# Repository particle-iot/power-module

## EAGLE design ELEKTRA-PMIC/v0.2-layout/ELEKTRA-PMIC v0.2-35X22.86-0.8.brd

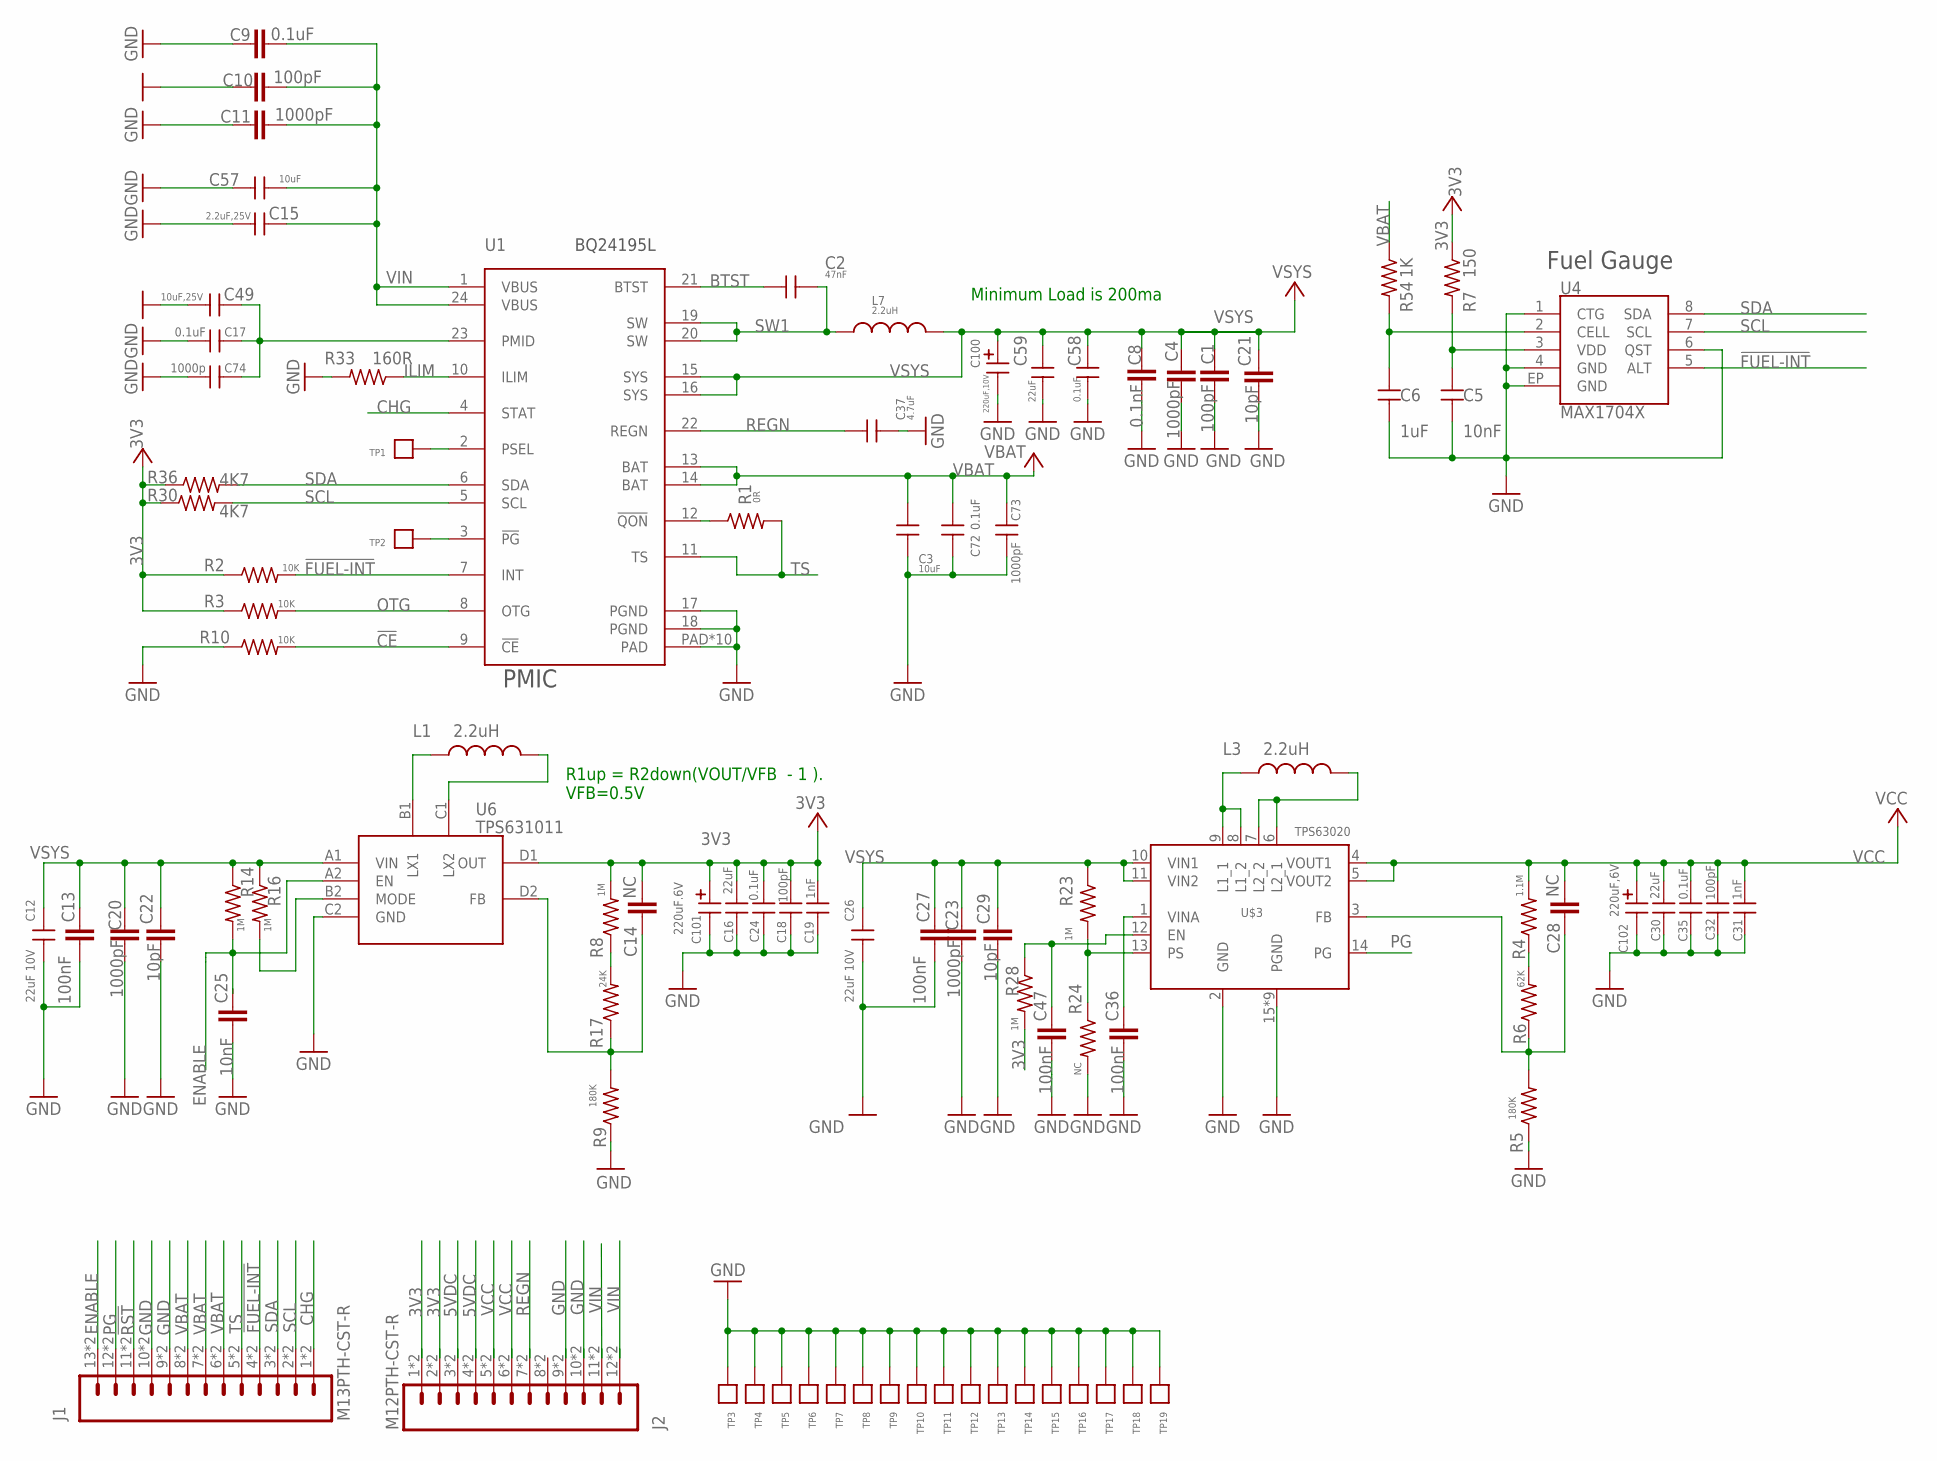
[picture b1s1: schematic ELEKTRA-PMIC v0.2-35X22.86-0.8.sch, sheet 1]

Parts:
C1, C10: 100pF; C0402_B
C2: 47nF; C-0402
C3: 10uF; C0805
C4, C11, C20, C23: 1000pF; C0402_B
C5: 10nF; C0402
C6: 1uF; C0402
C8: 0.1nF; C0402_B
C9: 0.1uF; C0402_B
C12, C26: 22uF 10V; C0805
C13, C27, C36, C47: 100nF; C0402_B
C14, C28: NC; C0402_B
C15: 2.2uF,25V; C-0603A
C16, C30: 22uF; C-0603A
C17, C24, C35, C58: 0.1uF; C0402
C18, C32: 100pF; C0402
C19, C31: 1nF; C0402
C21, C22, C29: 10pF; C0402_B
C25: 10nF; C0402_B
C37: 4.7uF; C0402
C49: 10uF,25V; C-0603A
C57: 10uF; C-0603A
C59: 22uF; C0603
C72: 0.1uF; C-0402
C73: 1000pF; C-0402
C74: 1000p; C-0402
C100: 220uF,10V; CASE-B
C101: 220uF.6V; CASE-B
C102: 220uF,6V; CASE-B
J1: M13PTH-CST-R; 1X13-CASTELLATED
J2: M12PTH-CST-R; 1X12-CASTELLATED
L1, L3: 2.2uH; INDUCTOR-VLS-E
L7: 2.2uH; INDUCTOR-4040
R1: 0R; R0402_B
R2, R3, R10: 10K; R0402_B
R4: 1.1M; R0402_B
R5, R9: 180K; R0402_B
R6: 62K; R0402_B
R7: 150; R0402_B
R8, R14, R16, R23, R28: 1M; R0402_B
R17: 24K; R0402_B
R24: NC; R0402_B
R30, R36: 4K7; R0402_B
R33: 160R; R0402_B
R54: 1K; R0402_B
TP1, TP2: TPTP; TP
TP3, TP4, TP5, TP6, TP7, TP8, TP9, TP10, TP11, TP12, TP13, TP14, TP15, TP16, TP17, TP18, TP19: TP0.4MM
U1: BQ24195L; QFN24
U4: MAX1704X; TDFN-8
U6: TPS631011; DSBGA
U$3: TPS63020

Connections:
3V3: C14.2, C16.1, C18.1, C19.1, C24.1, C101.P$1 (1), J2.1, J2.2, J2.@1 (1), J2.@2 (2), R2.1, R3.1, R7.1, R8.2, R28.2, R30.1, R36.1, U6.D1 (OUT)
5VDC: J2.3, J2.4, J2.@3 (3), J2.@4 (4)
!CE: R10.2, U1.9 (!CE)
!FUEL-INT: J1.4, J1.@4 (4), R2.2, U1.7 (INT), U4.5 (ALT)
!RST: J1.11, J1.@11 (11)
BTST: C2.1, U1.21 (BTST)
CHG: J1.1, J1.@1 (1), U1.4 (STAT)
ENABLE: C25.2, J1.13, J1.@13 (13), R14.2, U6.A2 (EN)
GND: C1.1, C3.2, C4.1, C5.2, C6.2, C8.1, C9.1, C10.1, C11.1, C12.2, C13.1, C15.2, C16.2, C17.1, C18.2, C19.2, C20.1, C21.1, C22.1, C23.1, C24.2, C25.1, C26.2, C27.1, C29.1, C30.2, C31.2, C32.2, C35.2, C36.1, C37.2, C47.1, C49.2, C57.2, C58.2, C59.2, C72.2, C73.2, C74.1, C100.P$2 (2), C101.P$2 (2), C102.P$2 (2), J1.9, J1.10, J1.@9 (9), J1.@10 (10), J2.9, J2.10, J2.@9 (9), J2.@10 (10), R5.1, R9.1, R10.1, R24.2, R33.2, TP3.P$1, TP4.P$1, TP5.P$1, TP6.P$1, TP7.P$1, TP8.P$1, TP9.P$1, TP10.P$1, TP11.P$1, TP12.P$1, TP13.P$1, TP14.P$1, TP15.P$1, TP16.P$1, TP17.P$1, TP18.P$1, TP19.P$1, U1.17 (PGND), U1.18 (PGND), U1.PAD, U1.PAD@1 (PAD), U1.PAD@2 (PAD), U1.PAD@3 (PAD), U1.PAD@4 (PAD), U1.PAD@5 (PAD), U1.PAD@6 (PAD), U1.PAD@7 (PAD), U1.PAD@8 (PAD), U1.PAD@9 (PAD), U4.1 (CTG), U4.4 (GND), U4.6 (QST), U4.EP (GND)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
ILIM: R33.1, U1.10 (ILIM)
unnamed: R1.1, U1.12 (!QON)
unnamed: C17.2, C49.1, C74.2, U1.23 (PMID)
unnamed: TP2.P$1, U1.3 (!PG)
unnamed: C14.1, R9.2, R17.1, U6.D2 (FB)
unnamed: C28.1, R5.2, R6.1, U$3.3 (FB)
unnamed: TP1.P$1, U1.2 (PSEL)
unnamed: R8.1, R17.2
unnamed: R4.1, R6.2
unnamed: L3.P$1 (1), U$3.8 (L1_2), U$3.9 (L1_1)
unnamed: L1.P$1 (1), U6.B1 (LX1)
unnamed: R16.2, U6.B2 (MODE)
unnamed: L3.P$2 (2), U$3.6 (L2_1), U$3.7 (L2_2)
unnamed: L1.P$2 (2), U6.C1 (LX2)
unnamed: C36.2, U$3.1 (VINA)
unnamed: C47.2, R28.1, U$3.12 (EN)
unnamed: R23.2, R24.1, U$3.13 (PS)
unnamed: C5.1, R7.2, U4.3 (VDD)
unnamed: C6.1, R54.2, U4.2 (CELL)
OTG: R3.2, U1.8 (OTG)
PG: J1.12, J1.@12 (12), U$3.14 (PG)
REGN: C37.1, J2.7, J2.@7 (7), U1.22 (REGN)
SCL: J1.2, J1.@2 (2), R30.2, U1.5 (SCL), U4.7 (SCL)
SDA: J1.3, J1.@3 (3), R36.2, U1.6 (SDA), U4.8 (SDA)
SW1: C2.2, L7.P$1 (1), U1.19 (SW), U1.20 (SW)
TS: J1.5, J1.@5 (5), R1.2, U1.11 (TS)
VBAT: C3.1, C72.1, C73.1, J1.6, J1.7, J1.8, J1.@6 (6), J1.@7 (7), J1.@8 (8), R54.1, U1.13 (BAT), U1.14 (BAT)
VCC: C28.2, C30.1, C31.1, C32.1, C35.1, C102.P$1 (1), J2.5, J2.6, J2.@5 (5), J2.@6 (6), R4.2, U$3.4 (VOUT1), U$3.5 (VOUT2)
VIN: C9.2, C10.2, C11.2, C15.1, C57.1, J2.11, J2.12, J2.@11 (11), J2.@12 (12), U1.1 (VBUS), U1.24 (VBUS)
VSYS: C1.2, C4.2, C8.2, C12.1, C13.2, C20.2, C21.2, C22.2, C23.2, C26.1, C27.2, C29.2, C58.1, C59.1, C100.P$1 (1), L7.P$2 (2), R14.1, R16.1, R23.1, U1.15 (SYS), U1.16 (SYS), U6.A1 (VIN), U$3.10 (VIN1), U$3.11 (VIN2)

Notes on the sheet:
Minimum Load is 200ma
PMIC
Fuel Gauge
R1up = R2down(VOUT/VFB - 1 ). VFB=0.5V

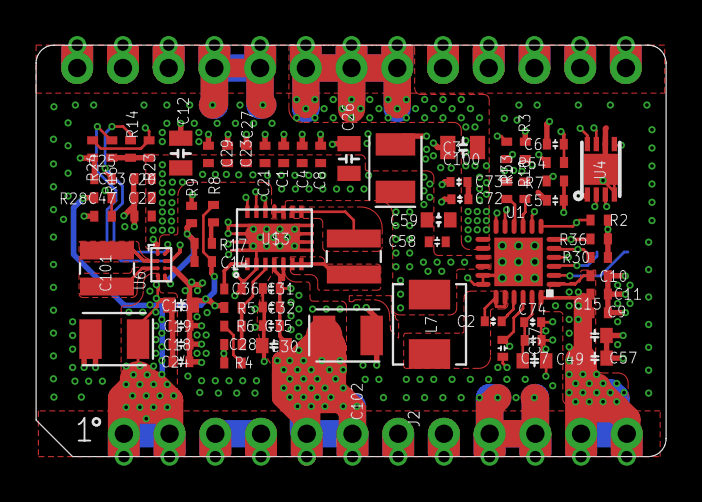
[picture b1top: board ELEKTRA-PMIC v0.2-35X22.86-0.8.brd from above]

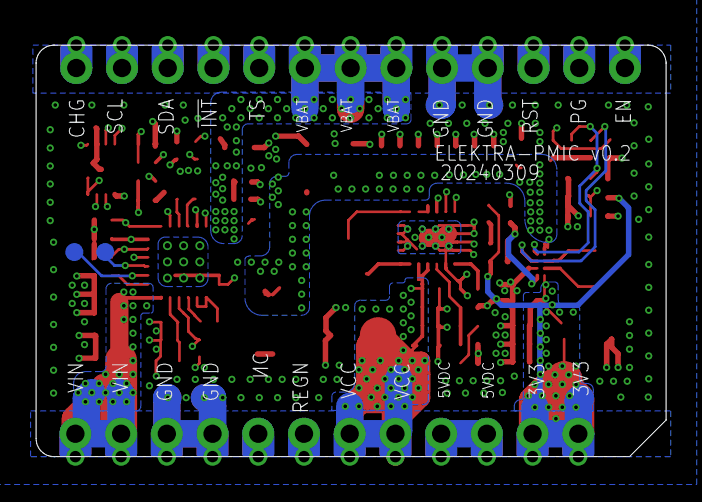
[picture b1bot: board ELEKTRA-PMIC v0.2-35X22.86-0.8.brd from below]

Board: 4 copper layers, 35.0 x 22.9 mm, 93 parts (19 on the bottom side), 39 nets.

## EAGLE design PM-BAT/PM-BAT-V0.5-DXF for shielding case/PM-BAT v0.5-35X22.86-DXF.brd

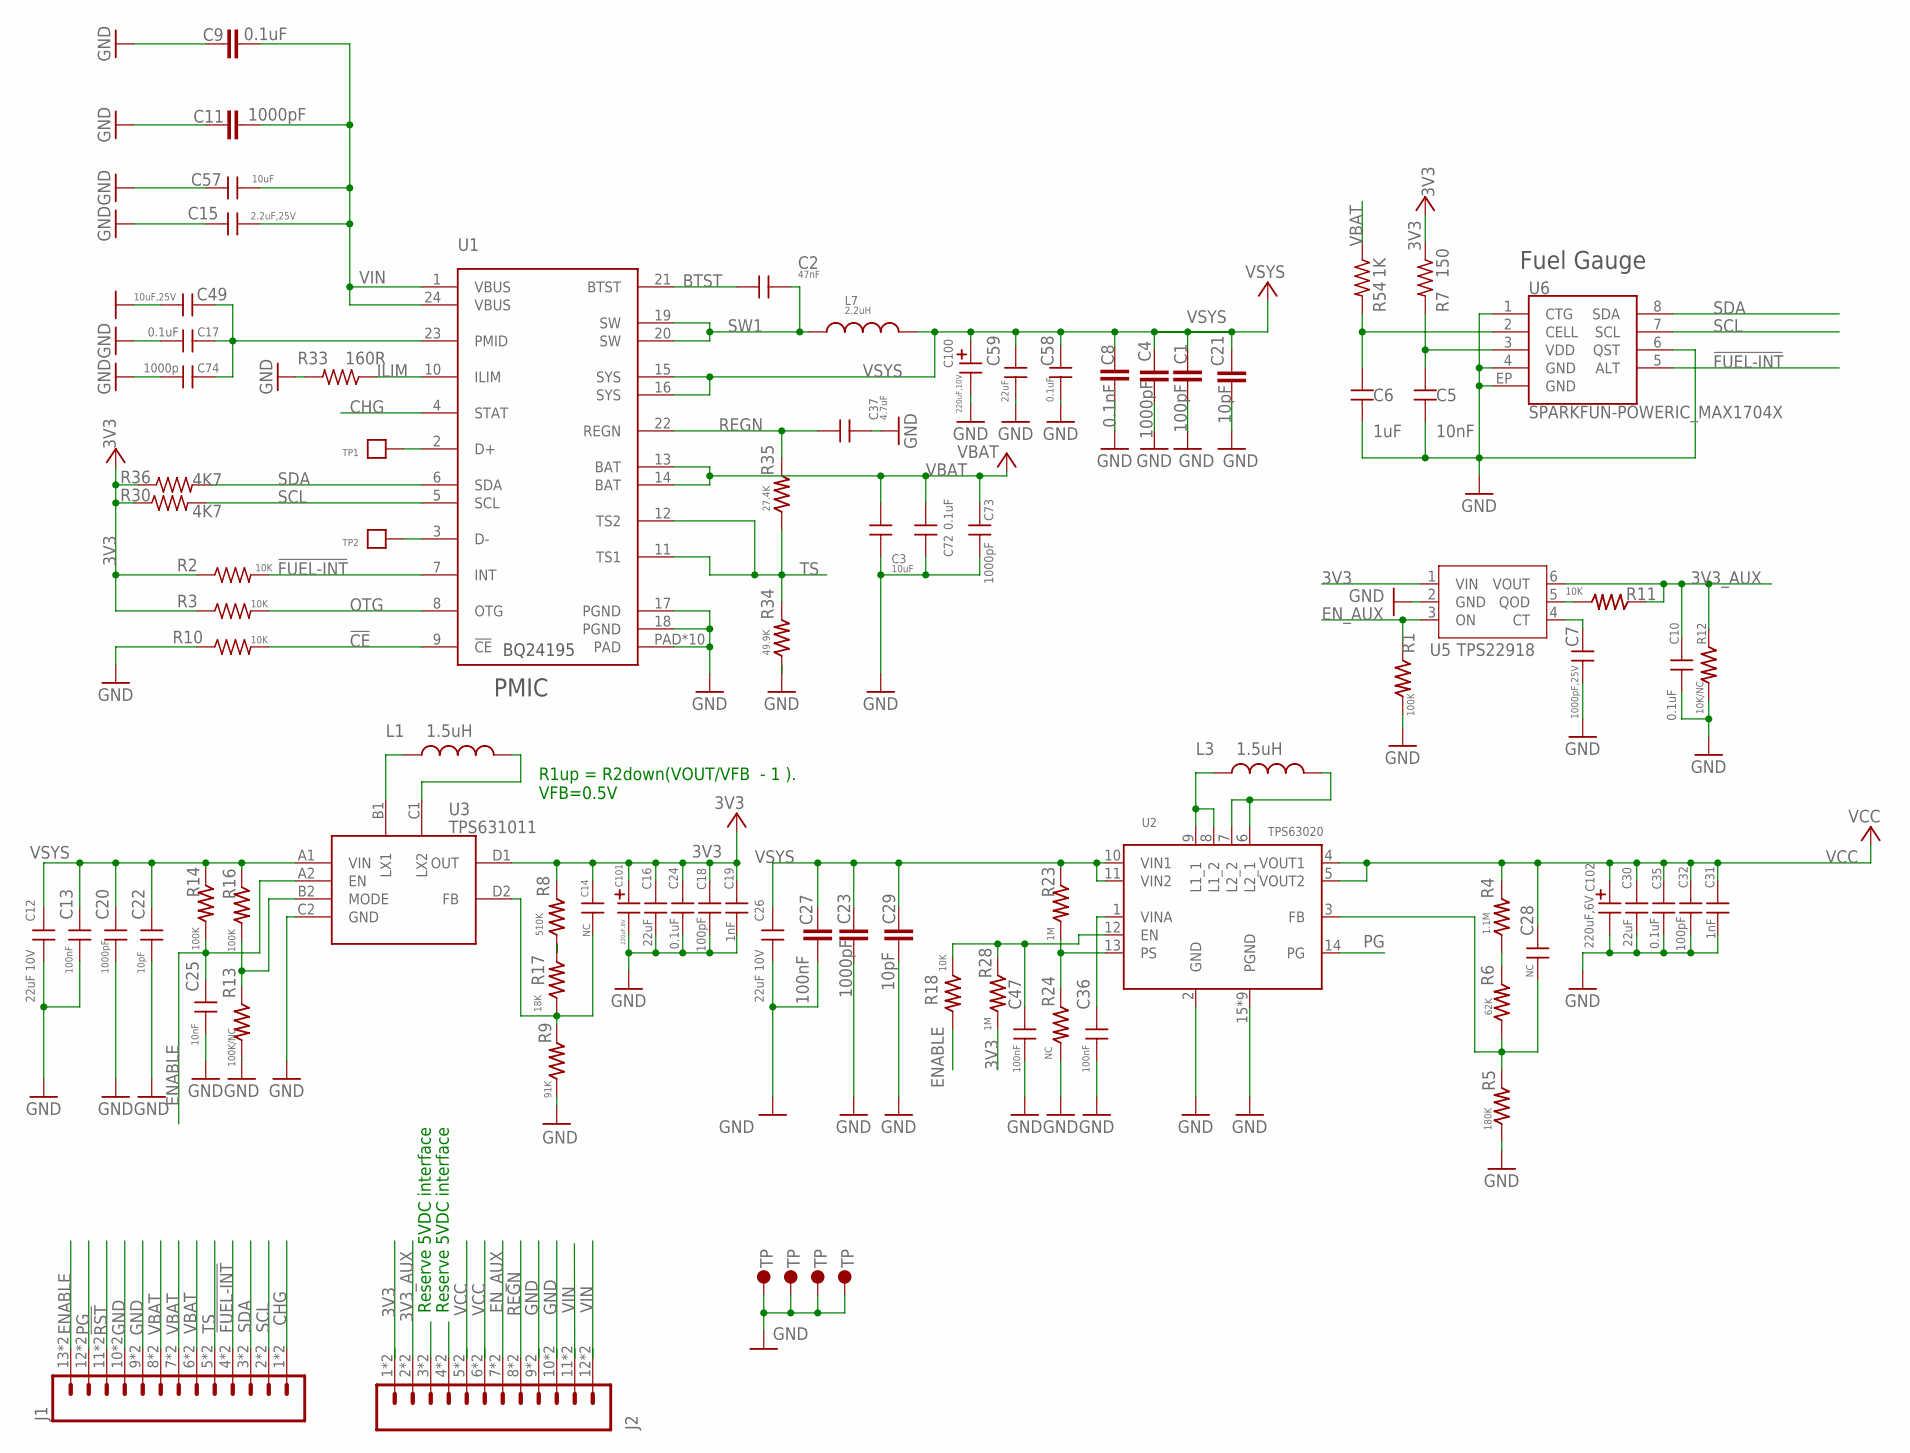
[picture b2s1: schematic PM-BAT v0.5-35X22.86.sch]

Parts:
C1: 100pF; C0402_B
C2: 47nF; C-0402
C3: 10uF; C0805
C4, C11, C23: 1000pF; C0402_B
C5: 10nF; C0402
C6: 1uF; C0402
C7: 1000pF,25V; C0402
C8: 0.1nF; C0402_B
C9: 0.1uF; C0402_B
C10: 0.1uF; C0201-N
C12, C26: 22uF 10V; C0603
C13, C36, C47: 100nF; C0201-N
C14, C28: NC; C0201-N
C15: 2.2uF,25V; C-0603A
C16, C30: 22uF; C-0603A
C17, C24, C35, C58: 0.1uF; C0402
C18, C32: 100pF; C0402
C19, C31: 1nF; C0402
C20: 1000pF; C0201-N
C21, C29: 10pF; C0402_B
C22: 10pF; C0201-N
C25: 10nF; C0201-N
C27: 100nF; C0402_B
C37: 4.7uF; C0402
C49: 10uF,25V; C-0603A
C57: 10uF; C-0603A
C59: 22uF; C0603
C72: 0.1uF; C-0402
C73: 1000pF; C-0402
C74: 1000p; C-0402
C100: 220uF,10V; CASE-B
C101: 220uF.6V; CASE-B
C102: 220uF,6V; CASE-B
J1: M13PTH-CST-R; 1X13-CASTELLATED
J2: M12PTH-CST-R; 1X12-CASTELLATED
L1, L3: 1.5uH; INDUCTOR-2520
L7: 2.2uH; INDUCTOR-4040
R1, R14, R16: 100K; R0201-N
R2, R3, R10: 10K; R0402_B
R4: 1.1M; R0201-N
R5: 180K; R0201-N
R6: 62K; R0201-N
R7: 150; R0402_B
R8: 510K; R0201-N
R9: 91K; R0201-N
R11, R18: 10K; R0201-N
R12: 10K/NC; R0201-N
R13: 100K/NC; R0201-N
R17: 18K; R0201-N
R23, R28: 1M; R0201-N
R24: NC; R0201-N
R30, R36: 4K7; R0402_B
R33: 160R; R0402_B
R34: 49.9K; R0201-N
R35: 27.4K; R0201-N
R54: 1K; R0402_B
TP1, TP2: TP1311MM; TP-1311MM
U1: BQ24195; ELECTRON_QFN24
U2: TPS63020
U3: TPS631011; DSBGA
U5: TPS22918; SOT-23-6
U6: SPARKFUN-POWERIC_MAX1704X; SPARKFUN-POWERIC_TDFN-8
U$1, U$2, U$4, U$5: TP; TP_2.33X1.37

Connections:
3V3: C14.1, C16.1, C18.1, C19.1, C24.1, C101.P$1 (1), J2.1, J2.@1 (1), R2.1, R3.1, R7.1, R8.2, R28.2, R30.1, R36.1, U3.D1 (OUT), U5.1 (VIN)
3V3_AUX: C10.1, J2.2, J2.@2 (2), R11.1, R12.1, U5.6 (VOUT)
!CE: R10.2, U1.9 (!CE)
!FUEL-INT: J1.4, J1.@4 (4), R2.2, U1.7 (INT), U6.5 (ALT)
!RST: J1.11, J1.@11 (11)
BTST: C2.1, U1.21 (BTST)
CHG: J1.1, J1.@1 (1), U1.4 (STAT)
ENABLE: C25.1, J1.13, J1.@13 (13), R14.2, R18.2, U3.A2 (EN)
EN_AUX: J2.7, J2.@7 (7), R1.1, U5.3 (ON)
GND: C1.1, C3.2, C4.1, C5.2, C6.2, C7.2, C8.1, C9.1, C10.2, C11.1, C12.2, C13.2, C15.2, C16.2, C17.1, C18.2, C19.2, C20.2, C21.1, C22.2, C23.1, C24.2, C25.2, C26.2, C27.1, C29.1, C30.2, C31.2, C32.2, C35.2, C36.2, C37.2, C47.2, C49.2, C57.2, C58.2, C59.2, C72.2, C73.2, C74.1, C100.P$2 (2), C101.P$2 (2), C102.P$2 (2), J1.9, J1.10, J1.@9 (9), J1.@10 (10), J2.9, J2.10, J2.@9 (9), J2.@10 (10), R1.2, R5.1, R9.1, R10.1, R12.2, R13.2, R24.2, R33.2, R34.1, U1.17 (PGND), U1.18 (PGND), U1.PAD, U1.PAD@1 (PAD), U1.PAD@2 (PAD), U1.PAD@3 (PAD), U1.PAD@4 (PAD), U1.PAD@5 (PAD), U1.PAD@6 (PAD), U1.PAD@7 (PAD), U1.PAD@8 (PAD), U1.PAD@9 (PAD), U2.2 (GND), U2.15 (PGND), U2.16 (PGND), U2.17 (PGND), U2.18 (PGND), U2.19 (PGND), U2.20 (PGND), U2.21 (PGND), U2.22 (PGND), U2.23 (PGND), U3.C2 (GND), U5.2 (GND), U6.1 (CTG), U6.4 (GND), U6.6 (QST), U6.EP (GND)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
ILIM: R33.1, U1.10 (ILIM)
unnamed: J2.3, J2.@3 (3)
unnamed: C17.2, C49.1, C74.2, U1.23 (PMID)
unnamed: TP2.P$1, U1.3 (D-)
unnamed: C14.2, R9.2, R17.1, U3.D2 (FB)
unnamed: C28.2, R5.2, R6.1, U2.3 (FB)
unnamed: TP1.P$1, U1.2 (D+)
unnamed: R8.1, R17.2
unnamed: R4.1, R6.2
unnamed: J2.4, J2.@4 (4)
unnamed: L3.1, U2.8 (L1_2), U2.9 (L1_1)
unnamed: L1.1, U3.B1 (LX1)
unnamed: R13.1, R16.2, U3.B2 (MODE)
unnamed: L3.2, U2.6 (L2_1), U2.7 (L2_2)
unnamed: L1.2, U3.C1 (LX2)
unnamed: C7.1, U5.4 (CT)
unnamed: C36.1, U2.1 (VINA)
unnamed: R11.2, U5.5 (QOD)
unnamed: C47.1, R18.1, R28.1, U2.12 (EN)
unnamed: R23.2, R24.1, U2.13 (PS)
unnamed: C5.1, R7.2, U6.3 (VDD)
unnamed: C6.1, R54.2, U6.2 (CELL)
OTG: R3.2, U1.8 (OTG)
PG: J1.12, J1.@12 (12), U2.14 (PG)
REGN: C37.1, J2.8, J2.@8 (8), R35.2, U1.22 (REGN)
SCL: J1.2, J1.@2 (2), R30.2, U1.5 (SCL), U6.7 (SCL)
SDA: J1.3, J1.@3 (3), R36.2, U1.6 (SDA), U6.8 (SDA)
SW1: C2.2, L7.P$1 (1), U1.19 (SW), U1.20 (SW)
TS: J1.5, J1.@5 (5), R34.2, R35.1, U1.11 (TS1), U1.12 (TS2)
VBAT: C3.1, C72.1, C73.1, J1.6, J1.7, J1.8, J1.@6 (6), J1.@7 (7), J1.@8 (8), R54.1, U1.13 (BAT), U1.14 (BAT)
VCC: C28.1, C30.1, C31.1, C32.1, C35.1, C102.P$1 (1), J2.5, J2.6, J2.@5 (5), J2.@6 (6), R4.2, U2.4 (VOUT1), U2.5 (VOUT2)
VIN: C9.2, C11.2, C15.1, C57.1, J2.11, J2.12, J2.@11 (11), J2.@12 (12), U1.1 (VBUS), U1.24 (VBUS)
VSYS: C1.2, C4.2, C8.2, C12.1, C13.1, C20.1, C21.2, C22.1, C23.2, C26.1, C27.2, C29.2, C58.1, C59.1, C100.P$1 (1), L7.P$2 (2), R14.1, R16.1, R23.1, U1.15 (SYS), U1.16 (SYS), U2.10 (VIN1), U2.11 (VIN2), U3.A1 (VIN)

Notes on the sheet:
PMIC
Fuel Gauge
R1up = R2down(VOUT/VFB - 1 ). VFB=0.5V
Reserve 5VDC interface

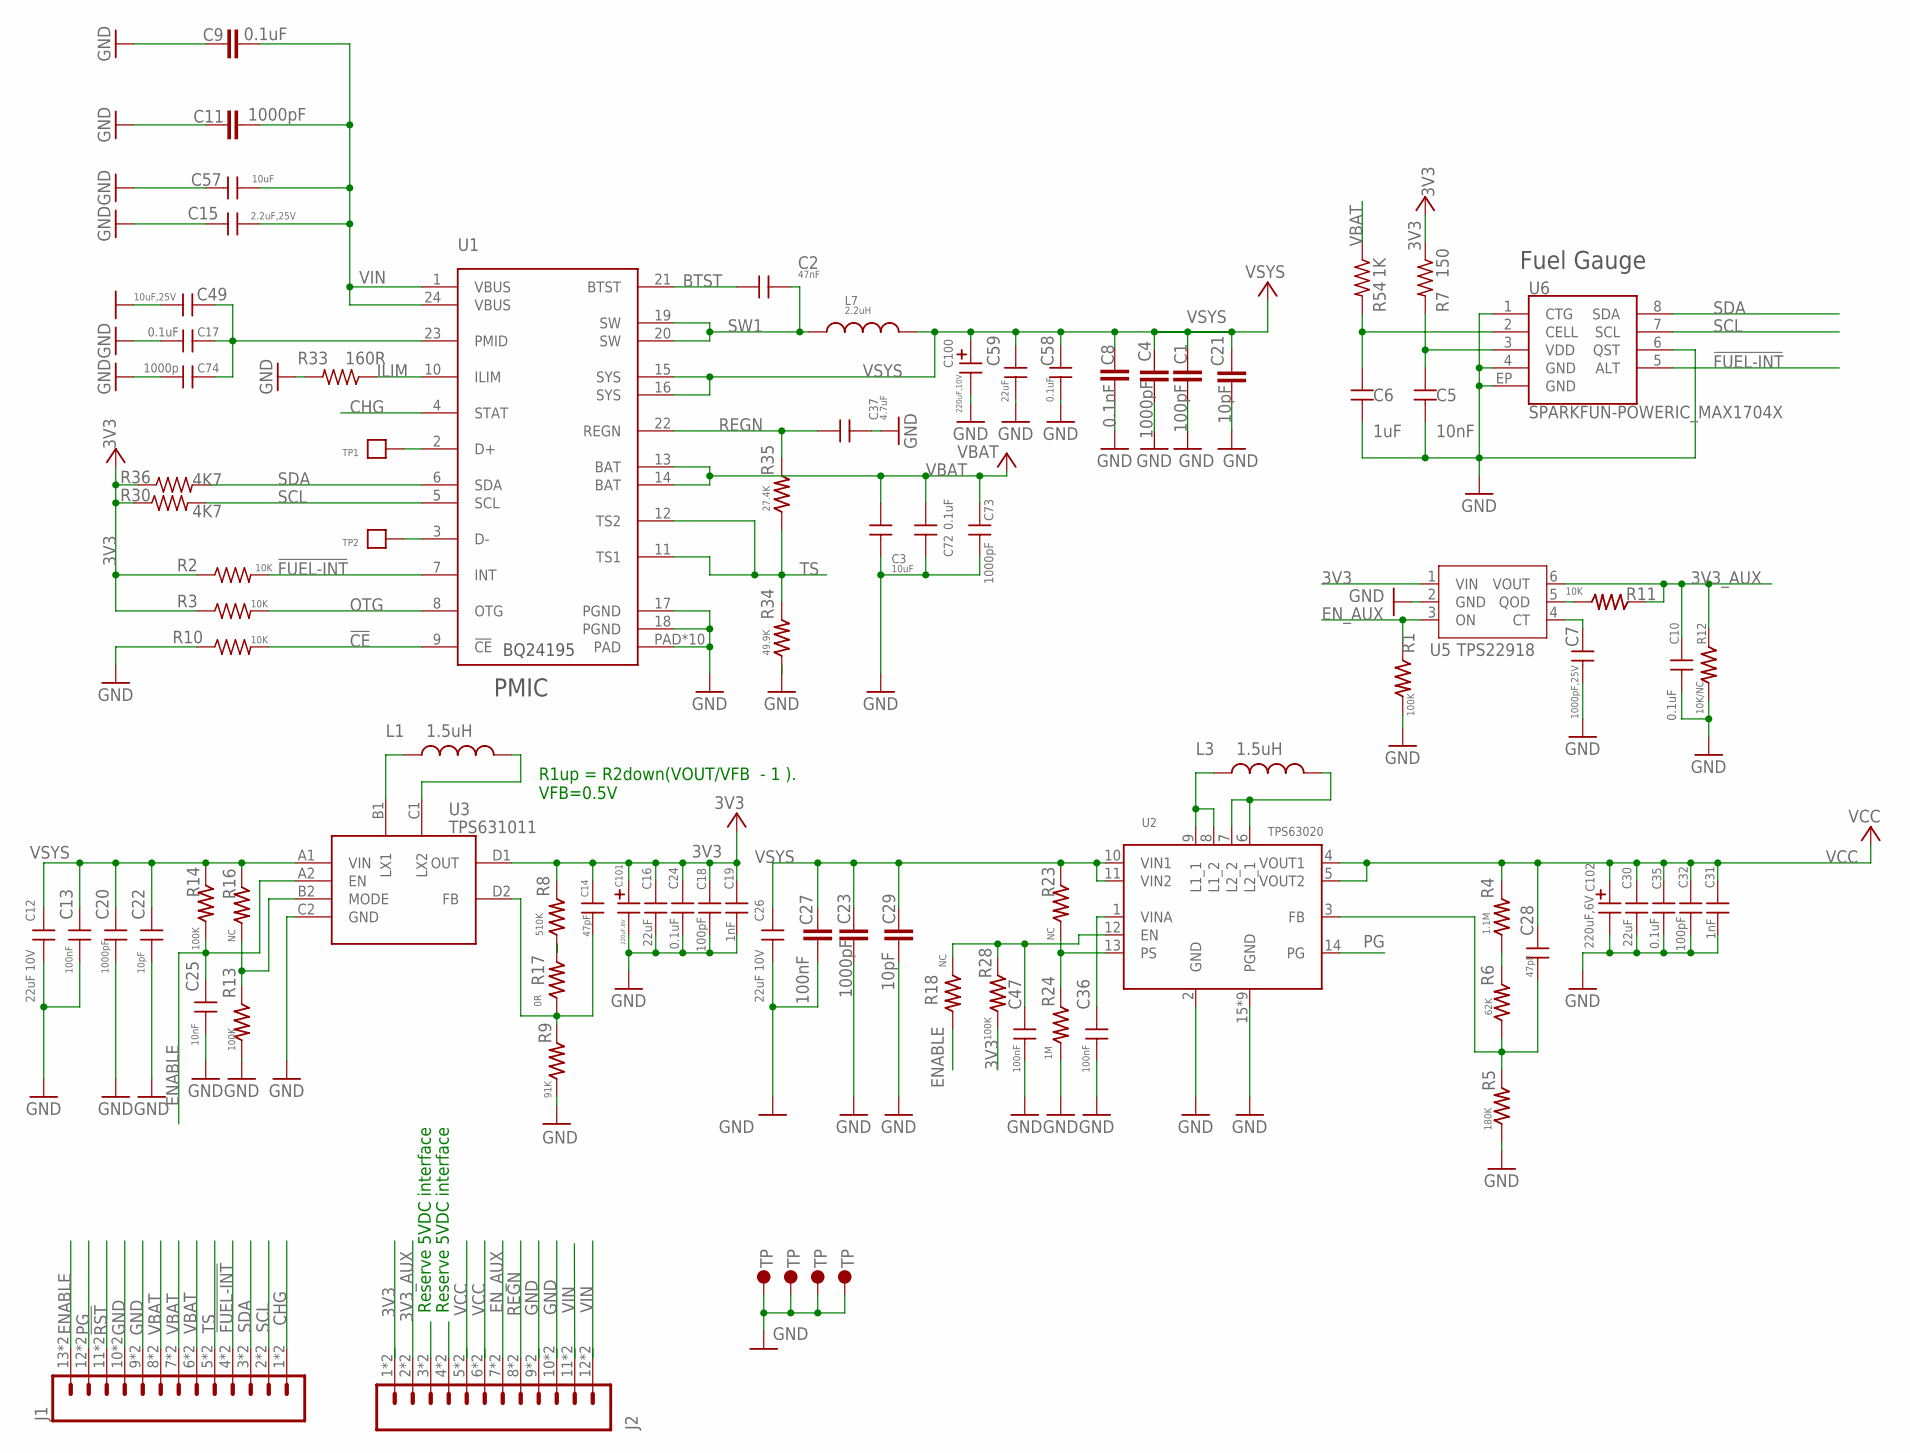
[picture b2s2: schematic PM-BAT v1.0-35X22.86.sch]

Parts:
C1: 100pF; C0402_B
C2: 47nF; C-0402
C3: 10uF; C0805
C4, C11, C23: 1000pF; C0402_B
C5: 10nF; C0402
C6: 1uF; C0402
C7: 1000pF,25V; C0402
C8: 0.1nF; C0402_B
C9: 0.1uF; C0402_B
C10: 0.1uF; C0201-N
C12, C26: 22uF 10V; C0603
C13, C36, C47: 100nF; C0201-N
C14, C28: 47pF; C0201-N
C15: 2.2uF,25V; C-0603A
C16, C30: 22uF; C-0603A
C17, C24, C35, C58: 0.1uF; C0402
C18, C32: 100pF; C0402
C19, C31: 1nF; C0402
C20: 1000pF; C0201-N
C21, C29: 10pF; C0402_B
C22: 10pF; C0201-N
C25: 10nF; C0201-N
C27: 100nF; C0402_B
C37: 4.7uF; C0402
C49: 10uF,25V; C-0603A
C57: 10uF; C-0603A
C59: 22uF; C0603
C72: 0.1uF; C-0402
C73: 1000pF; C-0402
C74: 1000p; C-0402
C100: 220uF,10V; CASE-B
C101: 220uF.6V; CASE-B
C102: 220uF,6V; CASE-B
J1: M13PTH-CST-R; 1X13-CASTELLATED
J2: M12PTH-CST-R; 1X12-CASTELLATED
L1, L3: 1.5uH; INDUCTOR-2520
L7: 2.2uH; INDUCTOR-4040
R1, R13, R14, R28: 100K; R0201-N
R2, R3, R10: 10K; R0402_B
R4: 1.1M; R0201-N
R5: 180K; R0201-N
R6: 62K; R0201-N
R7: 150; R0402_B
R8: 510K; R0201-N
R9: 91K; R0201-N
R11: 10K; R0201-N
R12: 10K/NC; R0201-N
R16, R18, R23: NC; R0201-N
R17: 0R; R0201-N
R24: 1M; R0201-N
R30, R36: 4K7; R0402_B
R33: 160R; R0402_B
R34: 49.9K; R0201-N
R35: 27.4K; R0201-N
R54: 1K; R0402_B
TP1, TP2: TP1311MM; TP-1311MM
U1: BQ24195; ELECTRON_QFN24
U2: TPS63020
U3: TPS631011; DSBGA
U5: TPS22918; SOT-23-6
U6: SPARKFUN-POWERIC_MAX1704X; SPARKFUN-POWERIC_TDFN-8
U$1, U$2, U$4, U$5: TP; TP_2.33X1.37

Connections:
3V3: C14.1, C16.1, C18.1, C19.1, C24.1, C101.P$1 (1), J2.1, J2.@1 (1), R2.1, R3.1, R7.1, R8.2, R28.2, R30.1, R36.1, U3.D1 (OUT), U5.1 (VIN)
3V3_AUX: C10.1, J2.2, J2.@2 (2), R11.1, R12.1, U5.6 (VOUT)
!CE: R10.2, U1.9 (!CE)
!FUEL-INT: J1.4, J1.@4 (4), R2.2, U1.7 (INT), U6.5 (ALT)
!RST: J1.11, J1.@11 (11)
BTST: C2.1, U1.21 (BTST)
CHG: J1.1, J1.@1 (1), U1.4 (STAT)
ENABLE: C25.1, J1.13, J1.@13 (13), R14.2, R18.2, U3.A2 (EN)
EN_AUX: J2.7, J2.@7 (7), R1.1, U5.3 (ON)
GND: C1.1, C3.2, C4.1, C5.2, C6.2, C7.2, C8.1, C9.1, C10.2, C11.1, C12.2, C13.2, C15.2, C16.2, C17.1, C18.2, C19.2, C20.2, C21.1, C22.2, C23.1, C24.2, C25.2, C26.2, C27.1, C29.1, C30.2, C31.2, C32.2, C35.2, C36.2, C37.2, C47.2, C49.2, C57.2, C58.2, C59.2, C72.2, C73.2, C74.1, C100.P$2 (2), C101.P$2 (2), C102.P$2 (2), J1.9, J1.10, J1.@9 (9), J1.@10 (10), J2.9, J2.10, J2.@9 (9), J2.@10 (10), R1.2, R5.1, R9.1, R10.1, R12.2, R13.2, R24.2, R33.2, R34.1, U1.17 (PGND), U1.18 (PGND), U1.PAD, U1.PAD@1 (PAD), U1.PAD@2 (PAD), U1.PAD@3 (PAD), U1.PAD@4 (PAD), U1.PAD@5 (PAD), U1.PAD@6 (PAD), U1.PAD@7 (PAD), U1.PAD@8 (PAD), U1.PAD@9 (PAD), U2.2 (GND), U2.15 (PGND), U2.16 (PGND), U2.17 (PGND), U2.18 (PGND), U2.19 (PGND), U2.20 (PGND), U2.21 (PGND), U2.22 (PGND), U2.23 (PGND), U3.C2 (GND), U5.2 (GND), U6.1 (CTG), U6.4 (GND), U6.6 (QST), U6.EP (GND)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
ILIM: R33.1, U1.10 (ILIM)
unnamed: J2.3, J2.@3 (3)
unnamed: C17.2, C49.1, C74.2, U1.23 (PMID)
unnamed: TP2.P$1, U1.3 (D-)
unnamed: C14.2, R9.2, R17.1, U3.D2 (FB)
unnamed: C28.2, R5.2, R6.1, U2.3 (FB)
unnamed: TP1.P$1, U1.2 (D+)
unnamed: R8.1, R17.2
unnamed: R4.1, R6.2
unnamed: J2.4, J2.@4 (4)
unnamed: L3.1, U2.8 (L1_2), U2.9 (L1_1)
unnamed: L1.1, U3.B1 (LX1)
unnamed: R13.1, R16.2, U3.B2 (MODE)
unnamed: L3.2, U2.6 (L2_1), U2.7 (L2_2)
unnamed: L1.2, U3.C1 (LX2)
unnamed: C7.1, U5.4 (CT)
unnamed: C36.1, U2.1 (VINA)
unnamed: R11.2, U5.5 (QOD)
unnamed: C47.1, R18.1, R28.1, U2.12 (EN)
unnamed: R23.2, R24.1, U2.13 (PS)
unnamed: C5.1, R7.2, U6.3 (VDD)
unnamed: C6.1, R54.2, U6.2 (CELL)
OTG: R3.2, U1.8 (OTG)
PG: J1.12, J1.@12 (12), U2.14 (PG)
REGN: C37.1, J2.8, J2.@8 (8), R35.2, U1.22 (REGN)
SCL: J1.2, J1.@2 (2), R30.2, U1.5 (SCL), U6.7 (SCL)
SDA: J1.3, J1.@3 (3), R36.2, U1.6 (SDA), U6.8 (SDA)
SW1: C2.2, L7.P$1 (1), U1.19 (SW), U1.20 (SW)
TS: J1.5, J1.@5 (5), R34.2, R35.1, U1.11 (TS1), U1.12 (TS2)
VBAT: C3.1, C72.1, C73.1, J1.6, J1.7, J1.8, J1.@6 (6), J1.@7 (7), J1.@8 (8), R54.1, U1.13 (BAT), U1.14 (BAT)
VCC: C28.1, C30.1, C31.1, C32.1, C35.1, C102.P$1 (1), J2.5, J2.6, J2.@5 (5), J2.@6 (6), R4.2, U2.4 (VOUT1), U2.5 (VOUT2)
VIN: C9.2, C11.2, C15.1, C57.1, J2.11, J2.12, J2.@11 (11), J2.@12 (12), U1.1 (VBUS), U1.24 (VBUS)
VSYS: C1.2, C4.2, C8.2, C12.1, C13.1, C20.1, C21.2, C22.1, C23.2, C26.1, C27.2, C29.2, C58.1, C59.1, C100.P$1 (1), L7.P$2 (2), R14.1, R16.1, R23.1, U1.15 (SYS), U1.16 (SYS), U2.10 (VIN1), U2.11 (VIN2), U3.A1 (VIN)

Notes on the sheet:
PMIC
Fuel Gauge
R1up = R2down(VOUT/VFB - 1 ). VFB=0.5V
Reserve 5VDC interface

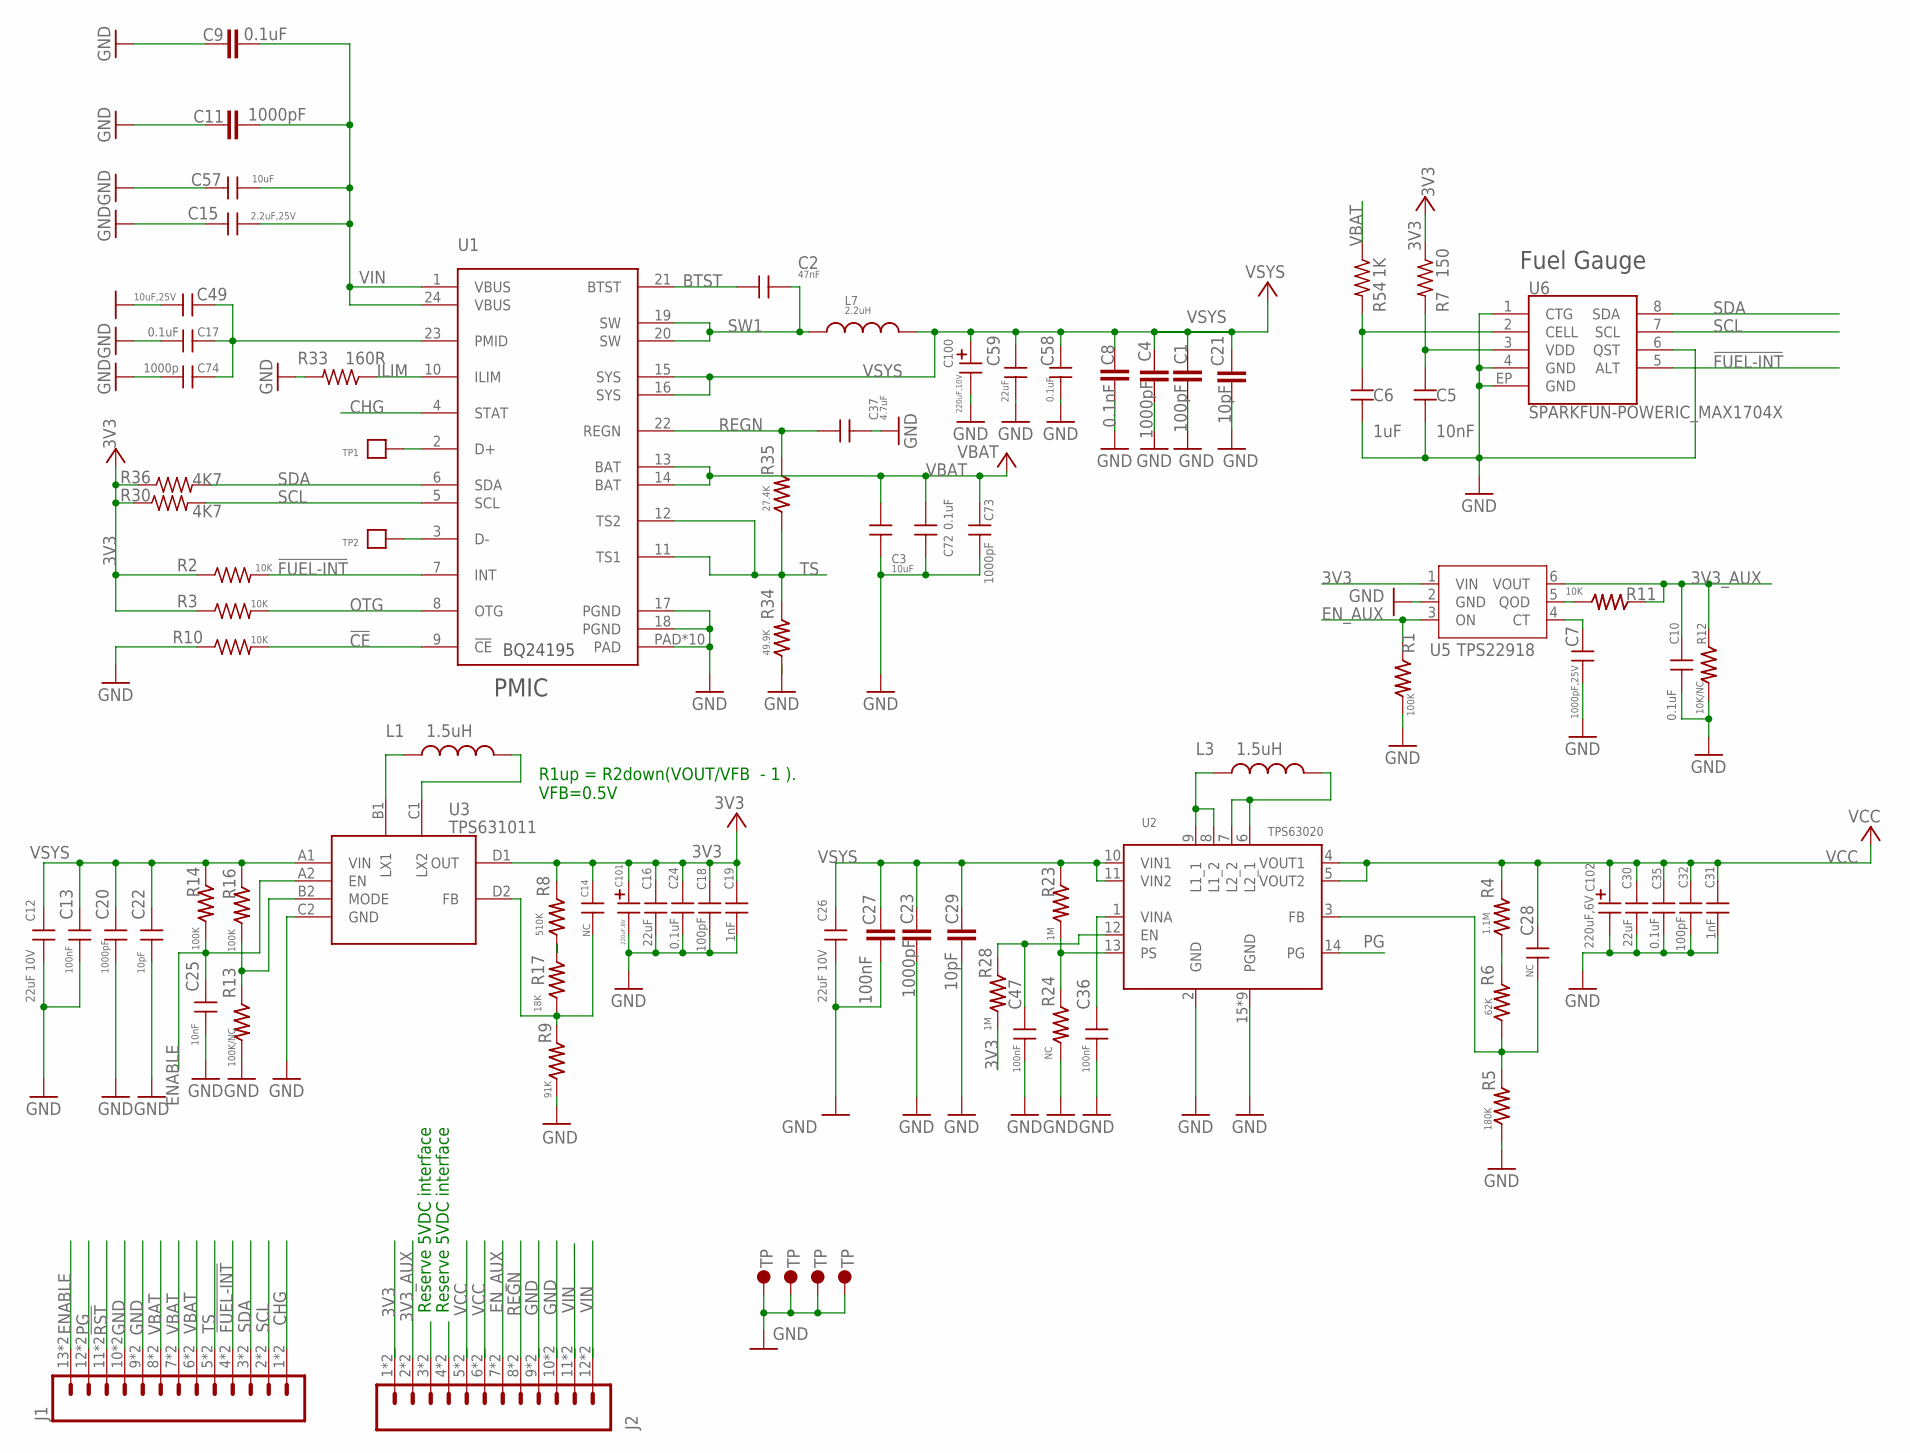
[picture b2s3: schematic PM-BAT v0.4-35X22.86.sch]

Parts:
C1: 100pF; C0402_B
C2: 47nF; C-0402
C3: 10uF; C0805
C4, C11, C23: 1000pF; C0402_B
C5: 10nF; C0402
C6: 1uF; C0402
C7: 1000pF,25V; C0402
C8: 0.1nF; C0402_B
C9: 0.1uF; C0402_B
C10: 0.1uF; C0201-N
C12, C26: 22uF 10V; C0603
C13, C36, C47: 100nF; C0201-N
C14, C28: NC; C0201-N
C15: 2.2uF,25V; C-0603A
C16, C30: 22uF; C-0603A
C17, C24, C35, C58: 0.1uF; C0402
C18, C32: 100pF; C0402
C19, C31: 1nF; C0402
C20: 1000pF; C0201-N
C21, C29: 10pF; C0402_B
C22: 10pF; C0201-N
C25: 10nF; C0201-N
C27: 100nF; C0402_B
C37: 4.7uF; C0402
C49: 10uF,25V; C-0603A
C57: 10uF; C-0603A
C59: 22uF; C0603
C72: 0.1uF; C-0402
C73: 1000pF; C-0402
C74: 1000p; C-0402
C100: 220uF,10V; CASE-B
C101: 220uF.6V; CASE-B
C102: 220uF,6V; CASE-B
J1: M13PTH-CST-R; 1X13-CASTELLATED
J2: M12PTH-CST-R; 1X12-CASTELLATED
L1, L3: 1.5uH; INDUCTOR-2520
L7: 2.2uH; INDUCTOR-4040
R1, R14, R16: 100K; R0201-N
R2, R3, R10: 10K; R0402_B
R4: 1.1M; R0201-N
R5: 180K; R0201-N
R6: 62K; R0201-N
R7: 150; R0402_B
R8: 510K; R0201-N
R9: 91K; R0201-N
R11: 10K; R0201-N
R12: 10K/NC; R0201-N
R13: 100K/NC; R0201-N
R17: 18K; R0201-N
R23, R28: 1M; R0201-N
R24: NC; R0201-N
R30, R36: 4K7; R0402_B
R33: 160R; R0402_B
R34: 49.9K; R0201-N
R35: 27.4K; R0201-N
R54: 1K; R0402_B
TP1, TP2: TP1311MM; TP-1311MM
U1: BQ24195; ELECTRON_QFN24
U2: TPS63020
U3: TPS631011; DSBGA
U5: TPS22918; SOT-23-6
U6: SPARKFUN-POWERIC_MAX1704X; SPARKFUN-POWERIC_TDFN-8
U$1, U$2, U$4, U$5: TP; TP_2.33X1.37

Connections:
3V3: C14.1, C16.1, C18.1, C19.1, C24.1, C101.P$1 (1), J2.1, J2.@1 (1), R2.1, R3.1, R7.1, R8.2, R28.2, R30.1, R36.1, U3.D1 (OUT), U5.1 (VIN)
3V3_AUX: C10.1, J2.2, J2.@2 (2), R11.1, R12.1, U5.6 (VOUT)
!CE: R10.2, U1.9 (!CE)
!FUEL-INT: J1.4, J1.@4 (4), R2.2, U1.7 (INT), U6.5 (ALT)
!RST: J1.11, J1.@11 (11)
BTST: C2.1, U1.21 (BTST)
CHG: J1.1, J1.@1 (1), U1.4 (STAT)
ENABLE: C25.1, J1.13, J1.@13 (13), R14.2, U3.A2 (EN); also elsewhere on the board
EN_AUX: J2.7, J2.@7 (7), R1.1, U5.3 (ON)
GND: C1.1, C3.2, C4.1, C5.2, C6.2, C7.2, C8.1, C9.1, C10.2, C11.1, C12.2, C13.2, C15.2, C16.2, C17.1, C18.2, C19.2, C20.2, C21.1, C22.2, C23.1, C24.2, C25.2, C26.2, C27.1, C29.1, C30.2, C31.2, C32.2, C35.2, C36.2, C37.2, C47.2, C49.2, C57.2, C58.2, C59.2, C72.2, C73.2, C74.1, C100.P$2 (2), C101.P$2 (2), C102.P$2 (2), J1.9, J1.10, J1.@9 (9), J1.@10 (10), J2.9, J2.10, J2.@9 (9), J2.@10 (10), R1.2, R5.1, R9.1, R10.1, R12.2, R13.2, R24.2, R33.2, R34.1, U1.17 (PGND), U1.18 (PGND), U1.PAD, U1.PAD@1 (PAD), U1.PAD@2 (PAD), U1.PAD@3 (PAD), U1.PAD@4 (PAD), U1.PAD@5 (PAD), U1.PAD@6 (PAD), U1.PAD@7 (PAD), U1.PAD@8 (PAD), U1.PAD@9 (PAD), U2.2 (GND), U2.15 (PGND), U2.16 (PGND), U2.17 (PGND), U2.18 (PGND), U2.19 (PGND), U2.20 (PGND), U2.21 (PGND), U2.22 (PGND), U2.23 (PGND), U3.C2 (GND), U5.2 (GND), U6.1 (CTG), U6.4 (GND), U6.6 (QST), U6.EP (GND)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
ILIM: R33.1, U1.10 (ILIM)
unnamed: J2.3, J2.@3 (3)
unnamed: C17.2, C49.1, C74.2, U1.23 (PMID)
unnamed: TP2.P$1, U1.3 (D-)
unnamed: C14.2, R9.2, R17.1, U3.D2 (FB)
unnamed: C28.2, R5.2, R6.1, U2.3 (FB)
unnamed: TP1.P$1, U1.2 (D+)
unnamed: R8.1, R17.2
unnamed: R4.1, R6.2
unnamed: J2.4, J2.@4 (4)
unnamed: L3.1, U2.8 (L1_2), U2.9 (L1_1)
unnamed: L1.1, U3.B1 (LX1)
unnamed: R13.1, R16.2, U3.B2 (MODE)
unnamed: L3.2, U2.6 (L2_1), U2.7 (L2_2)
unnamed: L1.2, U3.C1 (LX2)
unnamed: C7.1, U5.4 (CT)
unnamed: C36.1, U2.1 (VINA)
unnamed: R11.2, U5.5 (QOD)
unnamed 28: C47.1, R28.1, U2.12 (EN); also elsewhere on the board
unnamed: R23.2, R24.1, U2.13 (PS)
unnamed: C5.1, R7.2, U6.3 (VDD)
unnamed: C6.1, R54.2, U6.2 (CELL)
OTG: R3.2, U1.8 (OTG)
PG: J1.12, J1.@12 (12), U2.14 (PG)
REGN: C37.1, J2.8, J2.@8 (8), R35.2, U1.22 (REGN)
SCL: J1.2, J1.@2 (2), R30.2, U1.5 (SCL), U6.7 (SCL)
SDA: J1.3, J1.@3 (3), R36.2, U1.6 (SDA), U6.8 (SDA)
SW1: C2.2, L7.P$1 (1), U1.19 (SW), U1.20 (SW)
TS: J1.5, J1.@5 (5), R34.2, R35.1, U1.11 (TS1), U1.12 (TS2)
VBAT: C3.1, C72.1, C73.1, J1.6, J1.7, J1.8, J1.@6 (6), J1.@7 (7), J1.@8 (8), R54.1, U1.13 (BAT), U1.14 (BAT)
VCC: C28.1, C30.1, C31.1, C32.1, C35.1, C102.P$1 (1), J2.5, J2.6, J2.@5 (5), J2.@6 (6), R4.2, U2.4 (VOUT1), U2.5 (VOUT2)
VIN: C9.2, C11.2, C15.1, C57.1, J2.11, J2.12, J2.@11 (11), J2.@12 (12), U1.1 (VBUS), U1.24 (VBUS)
VSYS: C1.2, C4.2, C8.2, C12.1, C13.1, C20.1, C21.2, C22.1, C23.2, C26.1, C27.2, C29.2, C58.1, C59.1, C100.P$1 (1), L7.P$2 (2), R14.1, R16.1, R23.1, U1.15 (SYS), U1.16 (SYS), U2.10 (VIN1), U2.11 (VIN2), U3.A1 (VIN)

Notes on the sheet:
PMIC
Fuel Gauge
R1up = R2down(VOUT/VFB - 1 ). VFB=0.5V
Reserve 5VDC interface

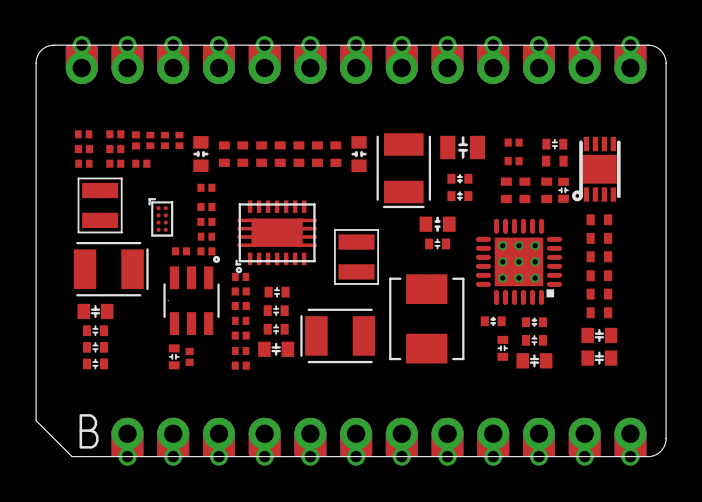
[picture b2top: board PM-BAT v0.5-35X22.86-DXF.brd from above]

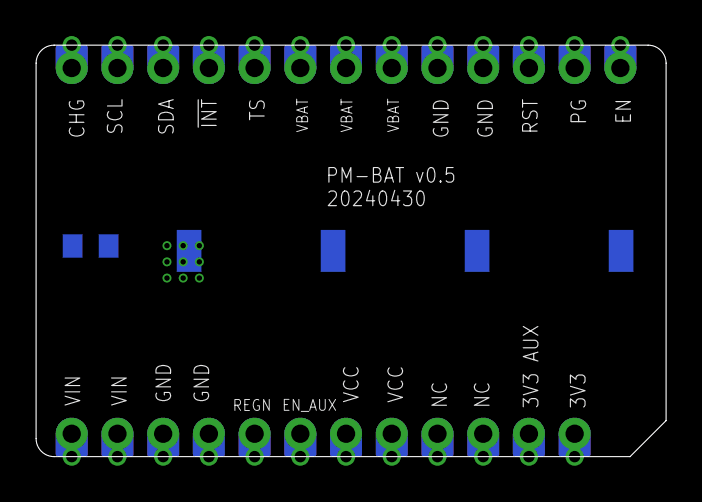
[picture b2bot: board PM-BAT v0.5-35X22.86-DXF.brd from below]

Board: 4 copper layers, 35.0 x 22.9 mm, 88 parts (6 on the bottom side), 43 nets.

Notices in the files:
parts and their libraries:
SparkFun-LED: Licensing: Creative Commons ShareAlike 4.0 International - https://creativecommons.org/licenses/by-sa/4.0
microbuilder: This work is placed in the public domain, and may be freely used for commercial and non-commercial work with the following conditions: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
